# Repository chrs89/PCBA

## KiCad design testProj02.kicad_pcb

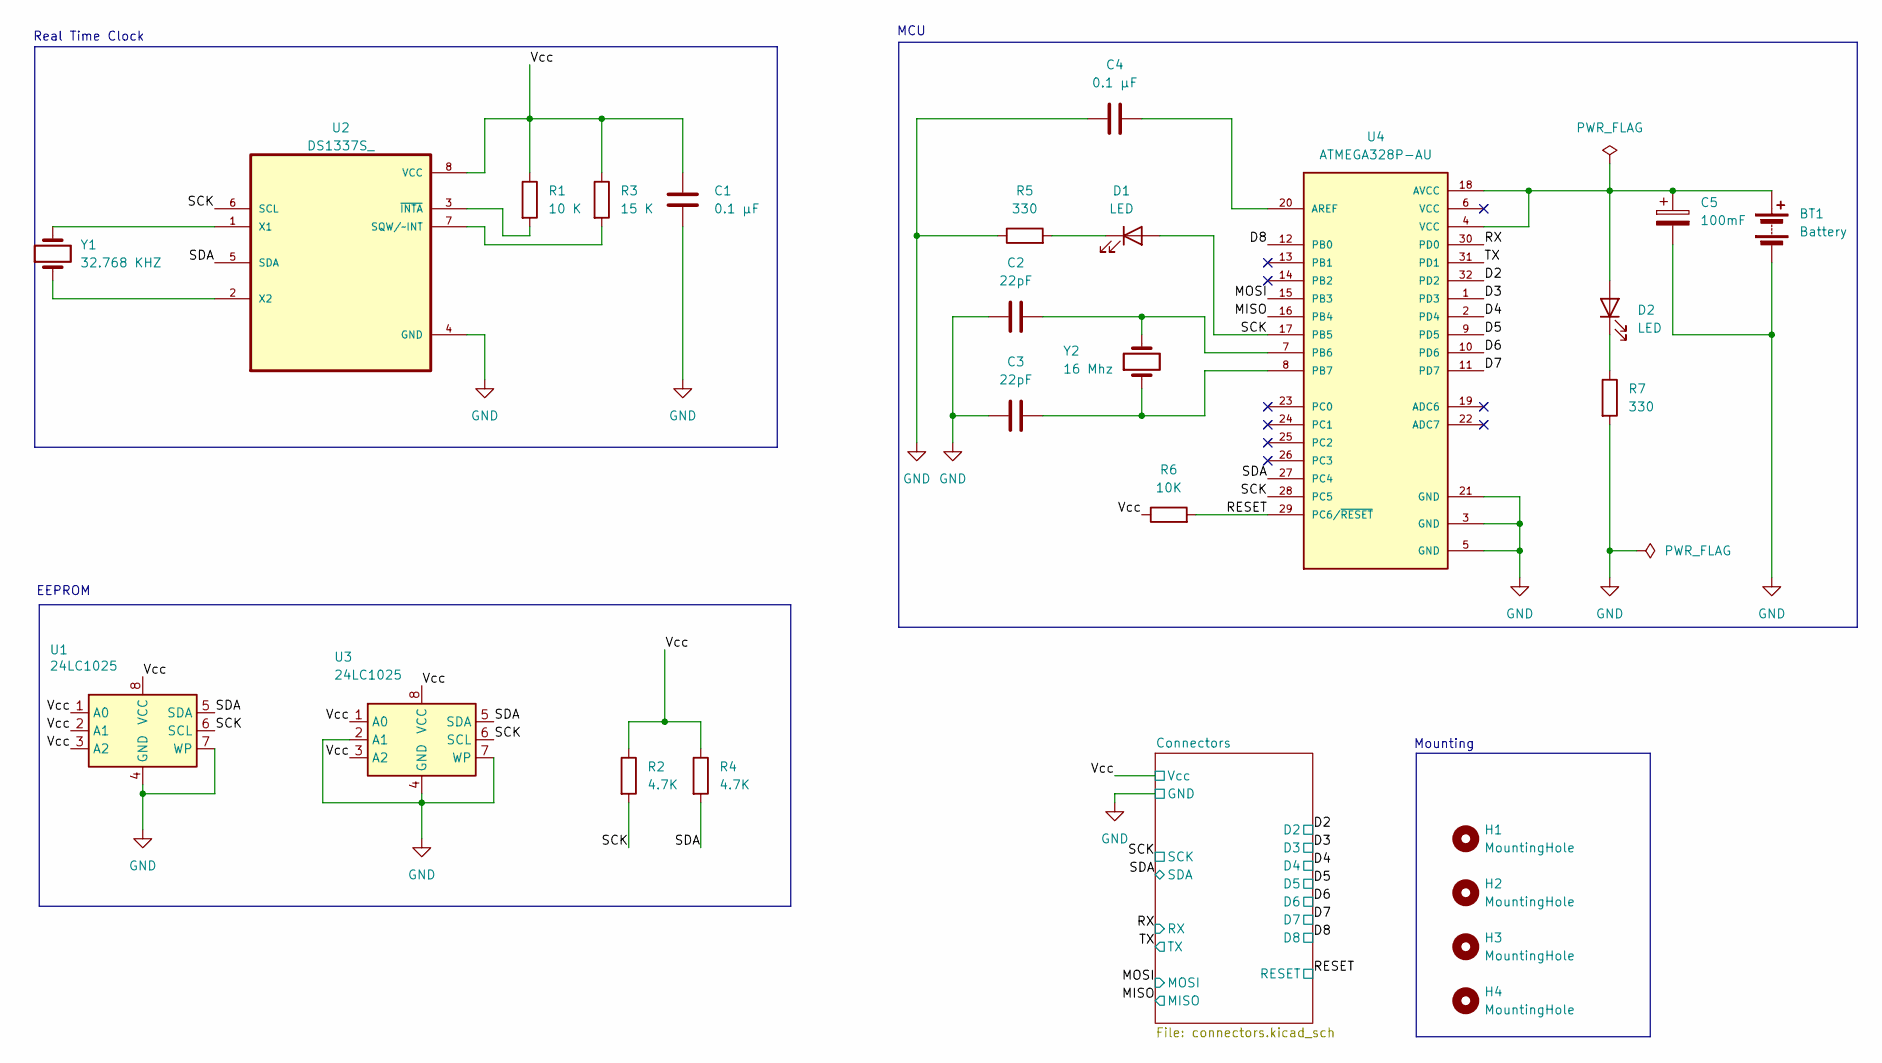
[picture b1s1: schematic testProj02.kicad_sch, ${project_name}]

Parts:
BT1: Battery; PinHeader_1x02_P2.54mm_Vertical
C1, C4: 0.1 µF; C_0805_2012Metric
C2, C3: 22pF; C_0805_2012Metric
C5: 100mF; C_0805_2012Metric
D1, D2: LED; LED_0805_2012Metric_Pad1.15x1.40mm_HandSolder
H1, H2, H3, H4: MountingHole; MountingHole_2.1mm
R1: 10 K; R_0805_2012Metric
R2, R4: 4.7K; R_0805_2012Metric
R3: 15 K; R_0805_2012Metric
R5, R7: 330; R_0805_2012Metric
R6: 10K; R_0805_2012Metric
U1, U3: 24LC1025; SOIC-8_5.3x5.3mm_P1.27mm
U2: DS1337S_; SOIC127P600X175-8N
U4: ATMEGA328P-AU; QFP80P900X900X120-32N; PARTREV 8271A
Y1: 32.768 KHZ; Crystal_SMD_5032-2Pin_5.0x3.2mm_HandSoldering
Y2: 16 Mhz; Crystal_SMD_5032-2Pin_5.0x3.2mm_HandSoldering

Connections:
/D2: U4.32 (PD2); also elsewhere on the board
/D3: U4.1 (PD3); also elsewhere on the board
/D4: U4.2 (PD4); also elsewhere on the board
/D5: U4.9 (PD5); also elsewhere on the board
/D6: U4.10 (PD6); also elsewhere on the board
/D7: U4.11 (PD7); also elsewhere on the board
/D8: U4.12 (PB0); also elsewhere on the board
/MISO: U4.16 (PB4); also elsewhere on the board
/MOSI: U4.15 (PB3); also elsewhere on the board
/RESET: R6.2, U4.29 (PC6/~RESET); also elsewhere on the board
/RX: U4.30 (PD0); also elsewhere on the board
/SCK: D1.2 (A), R2.2, U1.6 (SCL), U2.6 (SCL), U3.6 (SCL), U4.17 (PB5), U4.28 (PC5); also elsewhere on the board
/SDA: R4.2, U1.5 (SDA), U2.5 (SDA), U3.5 (SDA), U4.27 (PC4); also elsewhere on the board
/TX: U4.31 (PD1); also elsewhere on the board
/Vcc: C1.1, R1.1, R2.1, R3.1, R4.1, R6.1, U1.1 (A0), U1.2 (A1), U1.3 (A2), U1.8 (VCC), U2.8 (VCC), U3.1 (A0), U3.3 (A2), U3.8 (VCC); also elsewhere on the board
GND: BT1.2 (-), C1.2, C2.1, C3.1, C4.1, C5.2, R5.1, R7.2, U1.4 (GND), U1.7 (WP), U2.4 (GND), U3.2 (A1), U3.4 (GND), U3.7 (WP), U4.3 (GND), U4.5 (GND), U4.21 (GND); also elsewhere on the board
unnamed: BT1.1 (+), C5.1, D2.2 (A), U4.4 (VCC), U4.18 (AVCC)
unnamed: D1.1 (K), R5.2
unnamed: D2.1 (K), R7.1
unnamed: R3.2, U2.7 (SQW/~INT)
unnamed: U2.1 (X1), Y1.2
unnamed: U2.2 (X2), Y1.1
unnamed: R1.2, U2.3 (~INTA)
unnamed: C4.2, U4.20 (AREF)
unnamed: C2.2, U4.7 (PB6), Y2.2
unnamed: C3.2, U4.8 (PB7), Y2.1

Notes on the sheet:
EEPROM
Mounting
Real Time Clock
MCU

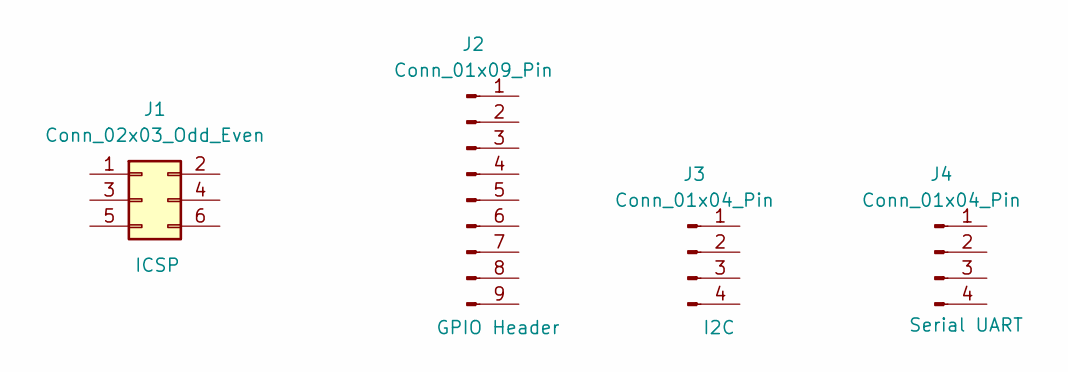
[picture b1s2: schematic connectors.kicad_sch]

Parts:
J1: Conn_02x03_Odd_Even; PinHeader_2x03_P2.54mm_Vertical
J2: Conn_01x09_Pin; PinHeader_1x09_P2.54mm_Vertical
J3, J4: Conn_01x04_Pin; PinHeader_1x04_P2.54mm_Vertical

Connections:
/D2: J2.1; also elsewhere on the board
/D3: J2.2; also elsewhere on the board
/D4: J2.3; also elsewhere on the board
/D5: J2.4; also elsewhere on the board
/D6: J2.5; also elsewhere on the board
/D7: J2.6; also elsewhere on the board
/D8: J2.7; also elsewhere on the board
/MISO: J1.1; also elsewhere on the board
/MOSI: J1.4; also elsewhere on the board
/RESET: J1.5; also elsewhere on the board
/RX: J4.3; also elsewhere on the board
/SCK: J1.3, J3.4; also elsewhere on the board
/SDA: J3.3; also elsewhere on the board
/TX: J4.4; also elsewhere on the board
/Vcc: J1.2, J2.9, J3.2, J4.2; also elsewhere on the board
GND: J1.6, J2.8, J3.1, J4.1; also elsewhere on the board

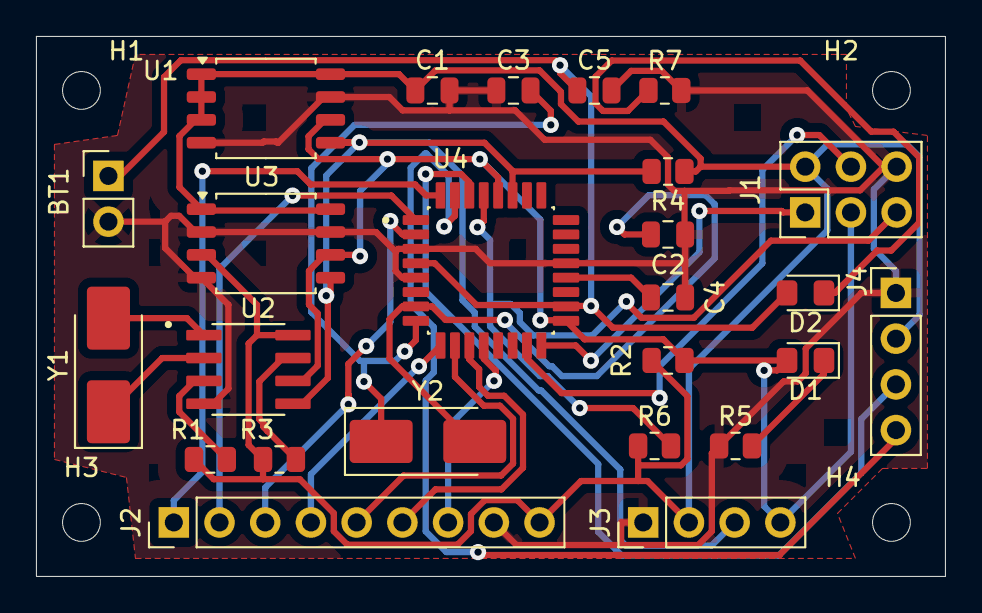
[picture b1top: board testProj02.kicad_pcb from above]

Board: 2 copper layers, 50.5 x 30.0 mm, 29 parts (0 on the bottom side), 26 nets.

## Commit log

2025-08-07 some changes
2025-08-07 Added component values
2025-08-07 assigned footprints
2025-08-07 Completed Wiring main sheet
2025-08-07 finalise schematic
2025-08-07 completed comments
2025-08-07 layout arrange components
2025-08-07 routing with Freerouting
2025-08-12 test
2025-08-12 2layer final
